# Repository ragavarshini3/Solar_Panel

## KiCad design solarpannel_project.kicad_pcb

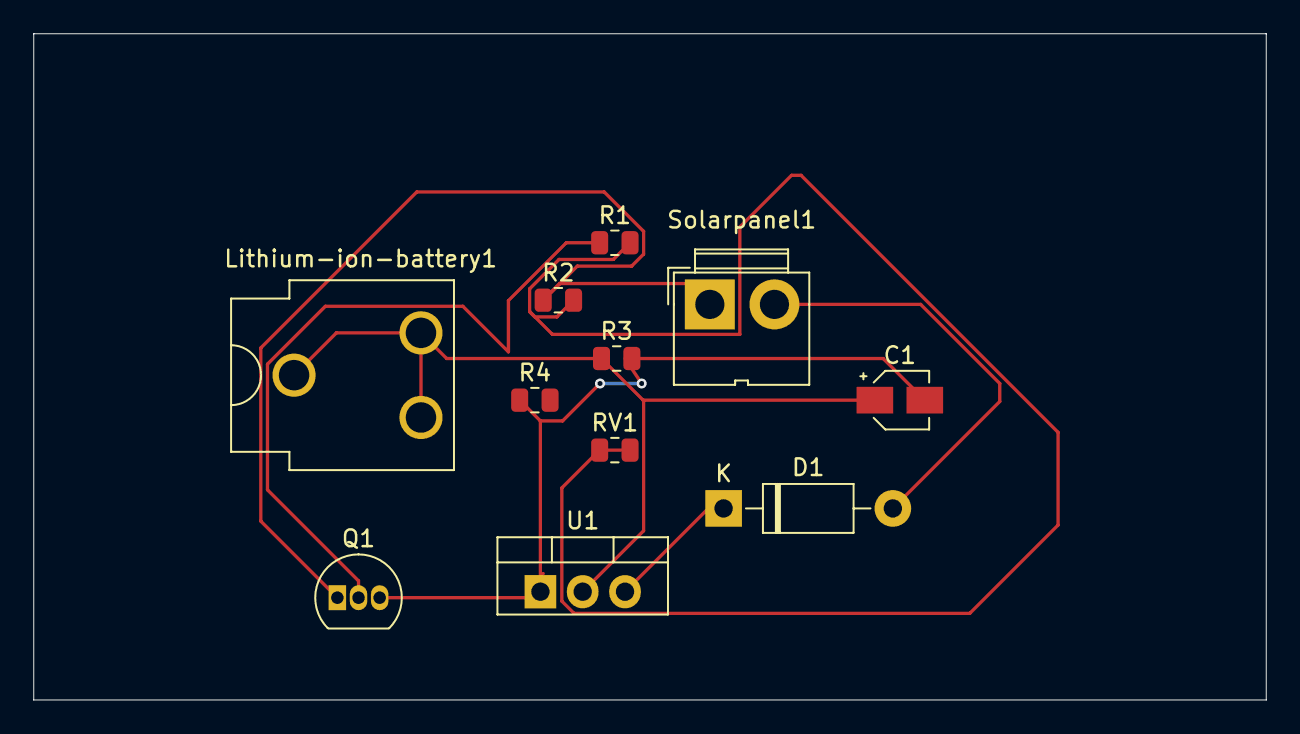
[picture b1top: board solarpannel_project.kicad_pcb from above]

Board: 2 copper layers, 74.0 x 40.0 mm, 11 parts (0 on the bottom side), 7 nets.

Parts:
C1: C_Small; CP_Elec_3x5.3
D1: 1N4001; D_DO-41_SOD81_P10.16mm_Horizontal
Lithium-ion-battery1: 3.7v; BatteryClip_Keystone_54_D16-19mm
Q1: BC548; TO-92_Inline
R1: 100; R_0805_2012Metric
R2: 0.5; R_0805_2012Metric
R3: 120; R_0805_2012Metric
R4: 470; R_0805_2012Metric
RV1: R_Potentiometer; R_0805_2012Metric
Solarpanel1: Conn_01x02; JWT_A3963_1x02_P3.96mm_Vertical
U1: LM317_TO-220; TO-220-3_Vertical

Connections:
unnamed: D1.2 (A), Solarpanel1.2
unnamed: D1.1 (K), U1.3 (VI)
unnamed: C1.1, Lithium-ion-battery1.1, R3.1, U1.2 (VO)
unnamed: R1.2, R2.2, RV1.1, RV1.2
unnamed: Q1.2 (B), R1.1
unnamed: Q1.1 (C), R2.1, Solarpanel1.1
unnamed: C1.2, Q1.3 (E), R3.2, R4.1, U1.1 (ADJ)
